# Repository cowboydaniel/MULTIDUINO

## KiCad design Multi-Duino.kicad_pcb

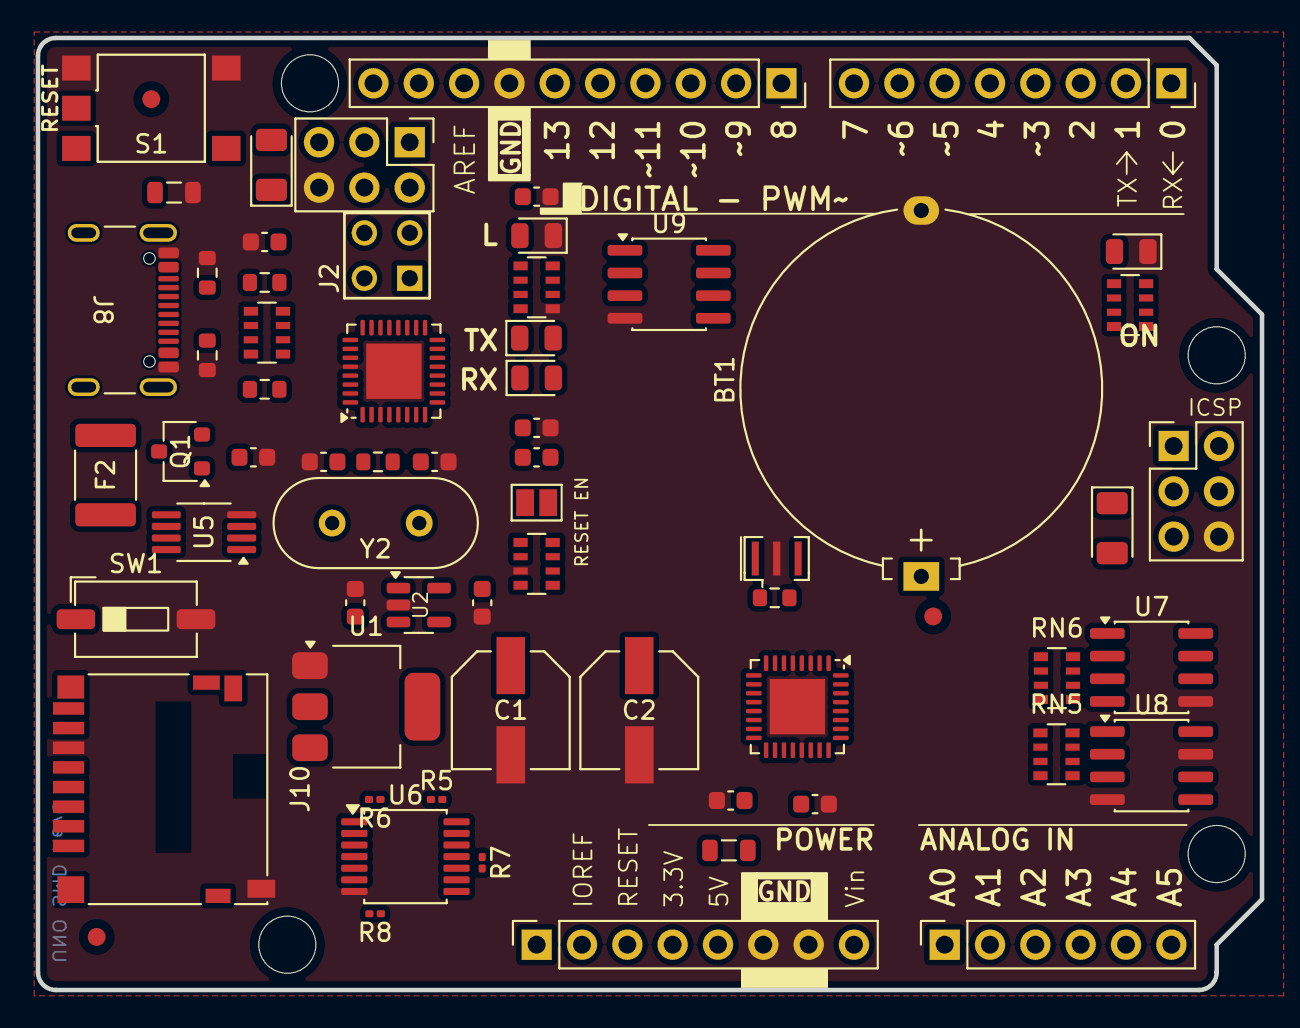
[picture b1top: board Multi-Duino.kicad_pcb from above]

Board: 4 copper layers, 68.6 x 53.3 mm, 67 parts (1 on the bottom side), 76 nets, no tracks yet.

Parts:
BT1: Battery_Cell; Battery_Panasonic_CR2032-HFN_Horizontal_CircularHoles
C1, C2: 47u; CAP_EEHZA1E470P
C3, C4, C6, C7, C8, C9, C12: 100n; C_0603_1608Metric
C5, C10: 1u; C_0603_1608Metric
C11, C13: 22p; C_0603_1608Metric
D2, D3: CD1206-S01575; D_1206_3216Metric
D4, D5, D6: YELLOW; LED_0805_2012Metric
D7: GREEN; LED_0805_2012Metric
F2: MF-MSMF050-2; Fuse_1812_4532Metric_Pad1.30x3.40mm_HandSolder
FB1: 1kΩ@100MHz; L_0805_2012Metric
FB2: 10uH; L_0805_2012Metric
FID1, FID2, FID3: Fiducial; Fiducial_1mm_Mask2mm
J1, J3: M20-9980345; PinHeader_2x03_P2.54mm_Vertical
J2: M20-9980245; CONN_M20-9980245_HRW
J4: PPTC101LFBN-RC; PinSocket_1x10_P2.54mm_Vertical
J5, J7: PPTC081LFBN-RC; PinSocket_1x08_P2.54mm_Vertical
J6: PPTC061LFBN-RC; PinSocket_1x06_P2.54mm_Vertical
J8: USB_C_Receptacle_USB2.0_16P; USB_C_Receptacle_GCT_USB4105-xx-A_16P_TopMnt_Horizontal
J10: Micro_SD_Card_Det1; microSD_HC_Hirose_DM3D-SF
JP1, JP2: SolderJumper_2_Open; SolderJumper-2_P1.3mm_Open_Pad1.0x1.5mm
Q1: FDN340P; SC-59
R1, R2: 1M; R_0603_1608Metric
R3, R4: 5k1; R_0603_1608Metric
R5, R6, R7, R8: 3.3K; R_0201_0603Metric
RN1: 10k; R_Array_Convex_4x0603
RN2, RN4: 1k; R_Array_Convex_4x0603
RN3: 22R; R_Array_Convex_4x0603
RN5, RN6: R_Pack04_Split; R_Array_Convex_4x0603
S1: TS06-667-30-BK-100-G-SMT-TR; SW_TS06-667-30-BK-100-G-SMT-TR
SW1: SW_DIP_x01; SW_DIP_SPSTx01_Slide_6.7x4.1mm_W6.73mm_P2.54mm_LowProfile_J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
U1: NCP1117-5.0_SOT223; SOT-223-3_TabPin2
U2: LP2985-3.3; SOT-23-5
U3: ATMEGA16U2-MU; VQFN-32-1EP_5x5mm_P0.5mm_EP3.1x3.1mm
U4: ATMEGA328P-MU; VQFN-32-1EP_5x5mm_P0.5mm_EP3.1x3.1mm
U5: LMV358IDGKR; MSOP-8_3x3mm_P0.65mm
U6: 74LVC125; TSSOP-14_4.4x5mm_P0.65mm
U7: DS3231MZ; SOIC-8_3.9x4.9mm_P1.27mm
U8: AT24CS32-SSHM; SOIC-8_3.9x4.9mm_P1.27mm
U9: 23AA02M-ISN; SOIC-8_3.9x4.9mm_P1.27mm
Y1: CSTNE16M0V530000R0; Resonator_SMD_Murata_CSTxExxV-3Pin_3.0x1.1mm
Y2: LFXTAL003240BULK; Crystal_HC49-4H_Vertical
Z1, Z2: 5pF@1MHz; R_0603_1608Metric

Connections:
32K: RN6.8 (R1.2), U7.1 (32KHZ)
+3.3V: C5.2, J7.4, J10.4 (VDD), U2.5 (VOUT), U5.2, U6.14 (VCC)
+5V: C1.1, C3.2, C4.1, C8.2, C9.1, D2.1 (K), D3.1 (K), FB2.1, J1.2, J3.2, J7.2, J7.5, Q1.2 (S), RN1.3 (R3.1), RN1.5 (R4.2), RN2.2 (R2.1), RN2.3 (R3.1), RN4.3 (R3.1), RN4.4 (R4.1), RN5.1 (R1.1), RN5.2 (R2.1), RN5.3 (R3.1), RN5.4 (R4.1), RN6.1 (R1.1), RN6.2 (R2.1), RN6.3 (R3.1), RN6.4 (R4.1), U1.2 (VO), U2.1 (VIN), U2.3 (ON/~OFF), U3.4 (VCC), U3.32 (AVCC), U4.4 (VCC), U4.6 (VCC__1), U5.8 (VCC+), U7.2 (VCC), U8.8 (VCC), U9.8 (V_{CC})
A0: J6.1, U4.23 (PC0)
A1: J6.2, U4.24 (PC1)
A2: J6.3, U4.25 (PC2)
A3: J6.4, U4.26 (PC3)
A4/SDA: J4.9, J6.5, RN6.5 (R4.2), U4.27 (PC4), U7.7 (SDA), U8.5 (SDA)
A5/SCL: J4.10, J6.6, RN6.7 (R2.2), U4.28 (PC5), U7.8 (SCL), U8.6 (SCL)
AREF: C6.1, J4.8, U4.20 (AREF)
AVCC: C12.1, FB2.2, U4.18 (AVCC)
CC1: J8.A5 (CC1), R3.1
CC2: J8.B5 (CC2), R4.1
CMP: RN1.1 (R1.1), RN1.2 (R2.1), U5.3
D+: J8.A6 (D+), J8.B6 (D+), RN3.5 (R4.2), Z1.1
D-: J8.A7 (D-), J8.B7 (D-), RN3.8 (R1.2), Z2.1
DTR: C7.1, RN2.4 (R4.1), U3.13 (PD7)
GATE_CMD: Q1.1 (G), U5.1
GND: BT1.2 (-), C1.2, C2.2, C3.1, C4.2, C5.1, C6.2, C8.1, C9.2, C10.1, C11.2, C12.2, C13.2, D4.1 (K), D7.1 (K), FB1.2, J1.6, J3.6, J4.7, J7.6, J7.7, J8.A1 (GND), J8.A12 (GND), J8.B1 (GND), J8.B12 (GND), J10.6 (VSS), J10.10 (SHIELD), JP2.1 (A), JP2.2 (B), R3.2, R4.2, RN1.7 (R2.2), RN2.5 (R4.2), S1.1, S1.2, SW1.2, U1.1 (GND), U2.2 (GND), U3.3 (GND), U3.28 (UGND), U3.33 (EXP), U4.3 (GND), U4.5 (GND__1), U4.21 (GND__2), U4.33 (EXP), U5.4 (GND), U6.7 (GND), U7.5 (GND), U8.4 (GND), U8.7 (WP), U9.4 (V_{SS}), Y1.2
IO0: J5.1, RN4.2 (R2.1), U4.30 (PD0)
IO1: J5.2, RN4.1 (R1.1), U4.31 (PD1)
IO2: J5.3, U4.32 (PD2)
IO3: J5.4, U4.1 (PD3)
IO4: J5.5, U4.2 (PD4)
IO5: J5.6, U4.9 (PD5)
IO6: J5.7, U4.10 (PD6)
IO7: J5.8, U4.11 (PD7)
IO8: J4.1, U4.12 (PB0)
IO9: J4.2, J10.9 (DET), U4.13 (PB1)
M8RXD: RN4.7 (R2.2), U3.9 (PD3)
M8TXD: RN4.8 (R1.2), U3.8 (PD2)
MISO: J3.1, J4.5, U4.16 (PB4), U6.11, U9.2 (SO/SIO1)
MISO2: J1.1, U3.17 (PB3)
MOSI: J3.4, J4.4, R6.1, U4.15 (PB3), U9.5 (SI/SIO0)
MOSI2: J1.4, U3.16 (PB2)
unnamed: BT1.1 (+), U7.6 (VBAT)
unnamed: D4.2 (A), RN2.1 (R1.1)
unnamed: D5.2 (A), RN2.6 (R3.2)
unnamed: D6.2 (A), RN2.7 (R2.2)
unnamed: D7.2 (A), RN4.5 (R4.2), RN4.6 (R3.2)
unnamed: J10.5 (CLK), U6.6
unnamed: J10.3 (CMD), U6.3
unnamed: J10.7 (DAT0), R5.1
unnamed: J10.2 (DAT3/CD), U6.8
unnamed: RN5.7 (R2.2), U8.1 (A0)
unnamed: RN5.6 (R3.2), U8.2 (A1)
unnamed: RN5.5 (R4.2), U8.3 (A2)
unnamed: R5.2, U6.12
unnamed: R6.2, U6.2
unnamed: R7.2, U6.9
unnamed: R8.2, U6.5
unnamed: RN2.8 (R1.2), U5.6, U5.7
unnamed: C13.1, R1.1, U3.2 (PC0), Y2.1
unnamed: C10.2, U3.27 (UCAP)
unnamed: C11.1, R1.2, U3.1 (XTAL1), Y2.2
unnamed: R2.2, U4.7 (PB6), Y1.3
unnamed: R2.1, U4.8 (PB7), Y1.1
PB4: J2.1, U3.18 (PB4)
PB5: J2.3, U3.19 (PB5)
PB6: J2.2, U3.20 (PB6)
PB7: J2.4, U3.21 (PB7)
RD+: RN3.4 (R4.1), U3.29 (D+)
RD-: RN3.1 (R1.1), U3.30 (D-)
RESET: C7.2, D2.2 (A), J3.5, J7.3, JP1.1 (A), JP1.2 (B), RN1.4 (R4.1), S1.3, S1.4, U4.29 (PC6/~RESET)
RESET2: D3.2 (A), J1.5, RN1.6 (R3.2), U3.24 (PC1//~RESET)
RXLED: D6.1 (K), U3.10 (PD4)
SCK: J3.3, J4.6, R8.1, U4.17 (PB5), U5.5, U9.6 (SCK)
SCK2: J1.3, U3.15 (PB1)
SQW: RN6.6 (R3.2), U7.3 (~INT/SQW)
SS: J4.3, R7.1, U4.14 (PB2), U6.13, U9.1 (~CS)
SW1: SW1.1, U6.1, U6.4, U6.10
TXLED: D5.1 (K), U3.11 (PD5)
USBVCC: F2.2, Q1.3 (D), U3.31 (UVCC)
USHIELD: FB1.1, J8.S1 (SHIELD), Z1.2, Z2.2
VCC: C2.1, J7.8, RN1.8 (R1.2), U1.3 (VI)
XUSB: F2.1, J8.A4 (VBUS), J8.A9 (VBUS), J8.B4 (VBUS), J8.B9 (VBUS)

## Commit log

2026-06-09 Update Multiduino v2 design
2026-06-09 Ignore KiCad temporary files
